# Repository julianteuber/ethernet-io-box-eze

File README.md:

View this project on [CADLAB.io](https://cadlab.io/project/2373). 

# ethernet_io_box_eze

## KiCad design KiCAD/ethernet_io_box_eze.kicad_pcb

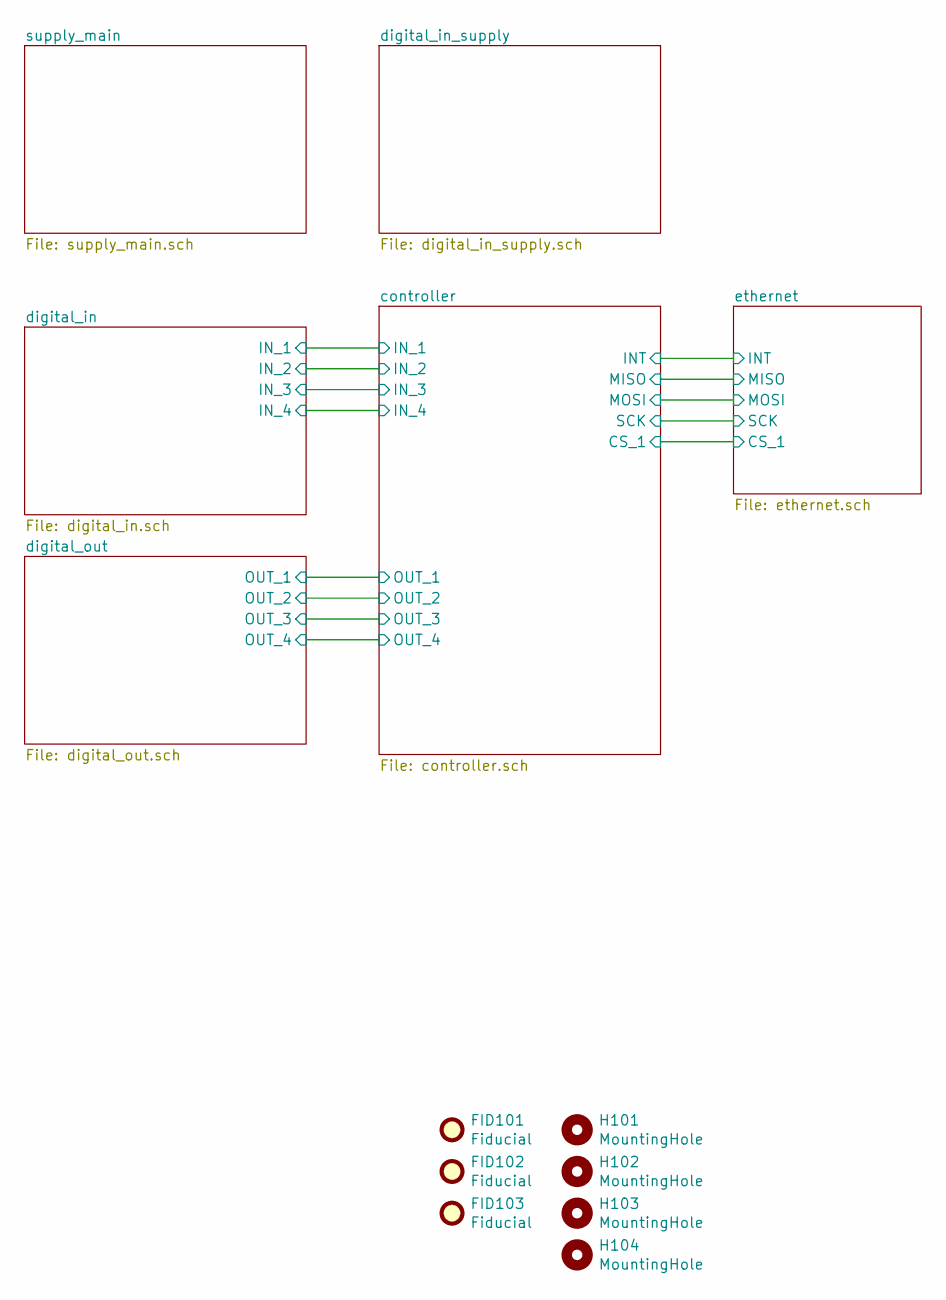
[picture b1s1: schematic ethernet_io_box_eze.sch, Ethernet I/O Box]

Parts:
FID101, FID102, FID103: Fiducial; Fiducial_0.5mm_Mask1mm
H101, H102, H103, H104: MountingHole; MountingHole_3mm

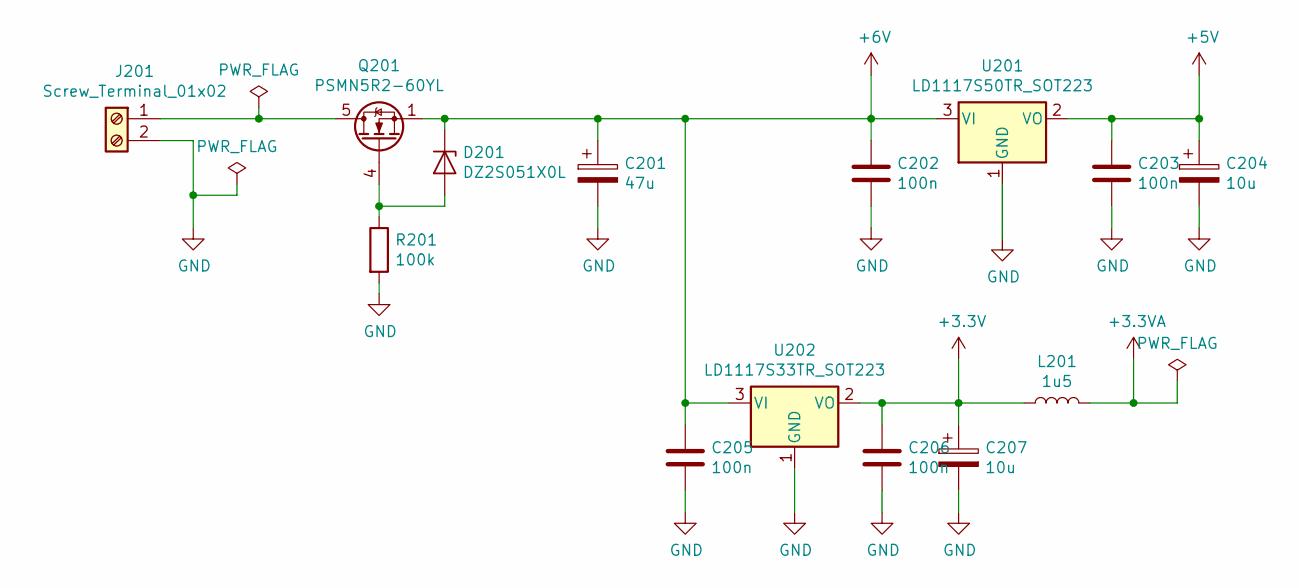
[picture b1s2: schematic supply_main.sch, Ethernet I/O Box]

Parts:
C201: 47u; CP_Elec_6.3x5.9
C202, C203, C205, C206: 100n; C_0805_2012Metric
C204, C207: 10u; CP_Elec_6.3x5.8
D201: DZ2S051X0L; D_SOD-523
J201: Screw_Terminal_01x02; PhoenixContact_GMSTBVA_2,5_2-G-7,62_1x02_P7.62mm_Vertical
L201: 1u5; L_0805_2012Metric
Q201: PSMN5R2-60YL; LFPAK56
R201: 100k; R_0805_2012Metric
U201: LD1117S50TR_SOT223; SOT-223-3_TabPin2
U202: LD1117S33TR_SOT223; SOT-223-3_TabPin2

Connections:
+3.3VA: L201.2; also elsewhere on the board
+3V3: C206.1, C207.1, L201.1, U202.2 (VO); also elsewhere on the board
+5V: C203.1, C204.1, U201.2 (VO); also elsewhere on the board
+6V: C201.1, C202.1, C205.1, D201.1 (K), Q201.1 (S), Q201.2 (S), Q201.3 (S), U201.3 (VI), U202.3 (VI); also elsewhere on the board
GND: C201.2, C202.2, C203.2, C204.2, C205.2, C206.2, C207.2, J201.2, R201.2, U201.1 (GND), U202.1 (GND); also elsewhere on the board
unnamed: D201.2 (A), Q201.4 (G), R201.1
unnamed: J201.1, Q201.5 (D)

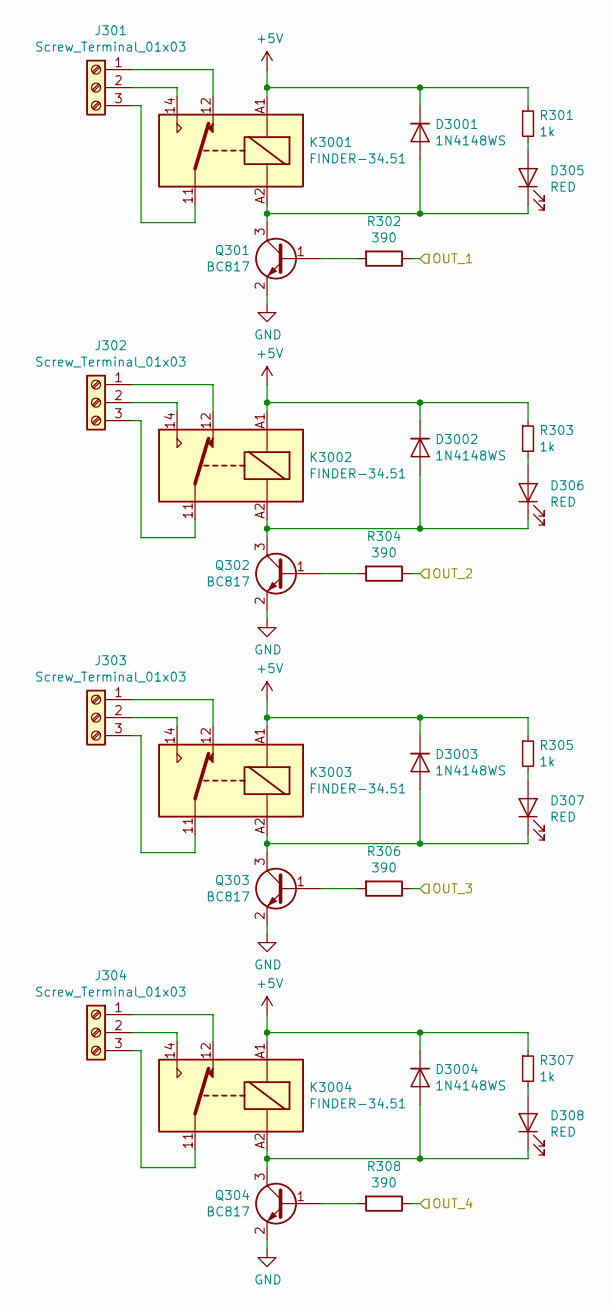
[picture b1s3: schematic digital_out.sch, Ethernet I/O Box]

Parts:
D305, D306, D307, D308: RED; LED_0805_2012Metric
D3001, D3002, D3003, D3004: 1N4148WS; D_SOD-123
J301, J302, J303, J304: Screw_Terminal_01x03; PhoenixContact_GMSTBVA_2,5_3-G-7,62_1x03_P7.62mm_Vertical
K3001, K3002, K3003, K3004: FINDER-34.51; Relay_SPDT_Finder_34.51_Vertical
Q301, Q302, Q303, Q304: BC817; SOT-23
R301, R303, R305, R307: 1k; R_0805_2012Metric
R302, R304, R306, R308: 390; R_0805_2012Metric

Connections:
+5V: D3001.1 (K), D3002.1 (K), D3003.1 (K), D3004.1 (K), K3001.A1, K3002.A1, K3003.A1, K3004.A1, R301.1, R303.1, R305.1, R307.1; also elsewhere on the board
/controller/OUT_1: R302.1; also elsewhere on the board
/controller/OUT_2: R304.1; also elsewhere on the board
/controller/OUT_3: R306.1; also elsewhere on the board
/controller/OUT_4: R308.1; also elsewhere on the board
GND: Q301.2 (E), Q302.2 (E), Q303.2 (E), Q304.2 (E); also elsewhere on the board
unnamed: D305.2 (A), R301.2
unnamed: D306.2 (A), R303.2
unnamed: D307.2 (A), R305.2
unnamed: D308.2 (A), R307.2
unnamed: D305.1 (K), D3001.2 (A), K3001.A2, Q301.3 (C)
unnamed: D306.1 (K), D3002.2 (A), K3002.A2, Q302.3 (C)
unnamed: D307.1 (K), D3003.2 (A), K3003.A2, Q303.3 (C)
unnamed: D308.1 (K), D3004.2 (A), K3004.A2, Q304.3 (C)
unnamed: J301.1, K3001.12
unnamed: J301.2, K3001.14
unnamed: J301.3, K3001.11
unnamed: J302.1, K3002.12
unnamed: J302.2, K3002.14
unnamed: J302.3, K3002.11
unnamed: J303.1, K3003.12
unnamed: J303.2, K3003.14
unnamed: J303.3, K3003.11
unnamed: J304.1, K3004.12
unnamed: J304.2, K3004.14
unnamed: J304.3, K3004.11
unnamed: Q301.1 (B), R302.2
unnamed: Q302.1 (B), R304.2
unnamed: Q303.1 (B), R306.2
unnamed: Q304.1 (B), R308.2

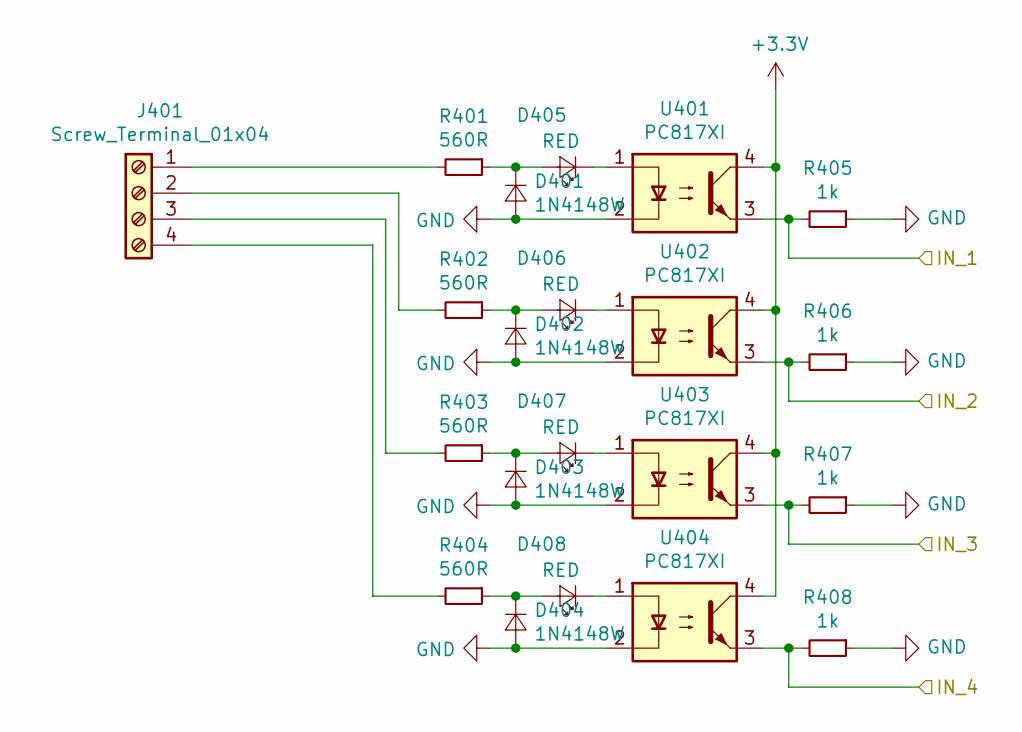
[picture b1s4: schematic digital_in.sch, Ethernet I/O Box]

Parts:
D401, D402, D403, D404: 1N4148W; D_SOD-123
D405, D406, D407, D408: RED; LED_0805_2012Metric
J401: Screw_Terminal_01x04; PhoenixContact_GMSTBVA_2,5_4-G-7,62_1x04_P7.62mm_Vertical
R401, R402, R403, R404: 560R; R_0805_2012Metric
R405, R406, R407, R408: 1k; R_0805_2012Metric
U401, U402, U403, U404: PC817XI; DIP-4_W8.89mm_SMDSocket_LongPads

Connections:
+3V3: U401.4, U402.4, U403.4, U404.4; also elsewhere on the board
/controller/IN_1: R405.2, U401.3; also elsewhere on the board
/controller/IN_2: R406.2, U402.3; also elsewhere on the board
/controller/IN_3: R407.2, U403.3; also elsewhere on the board
/controller/IN_4: R408.2, U404.3; also elsewhere on the board
GND: D401.2 (A), D402.2 (A), D403.2 (A), D404.2 (A), R405.1, R406.1, R407.1, R408.1, U401.2, U402.2, U403.2, U404.2; also elsewhere on the board
unnamed: D401.1 (K), D405.2 (A), R401.1
unnamed: D402.1 (K), D406.2 (A), R402.1
unnamed: D403.1 (K), D407.2 (A), R403.1
unnamed: D404.1 (K), D408.2 (A), R404.1
unnamed: D405.1 (K), U401.1
unnamed: D406.1 (K), U402.1
unnamed: D407.1 (K), U403.1
unnamed: D408.1 (K), U404.1
unnamed: J401.1, R401.2
unnamed: J401.2, R402.2
unnamed: J401.3, R403.2
unnamed: J401.4, R404.2

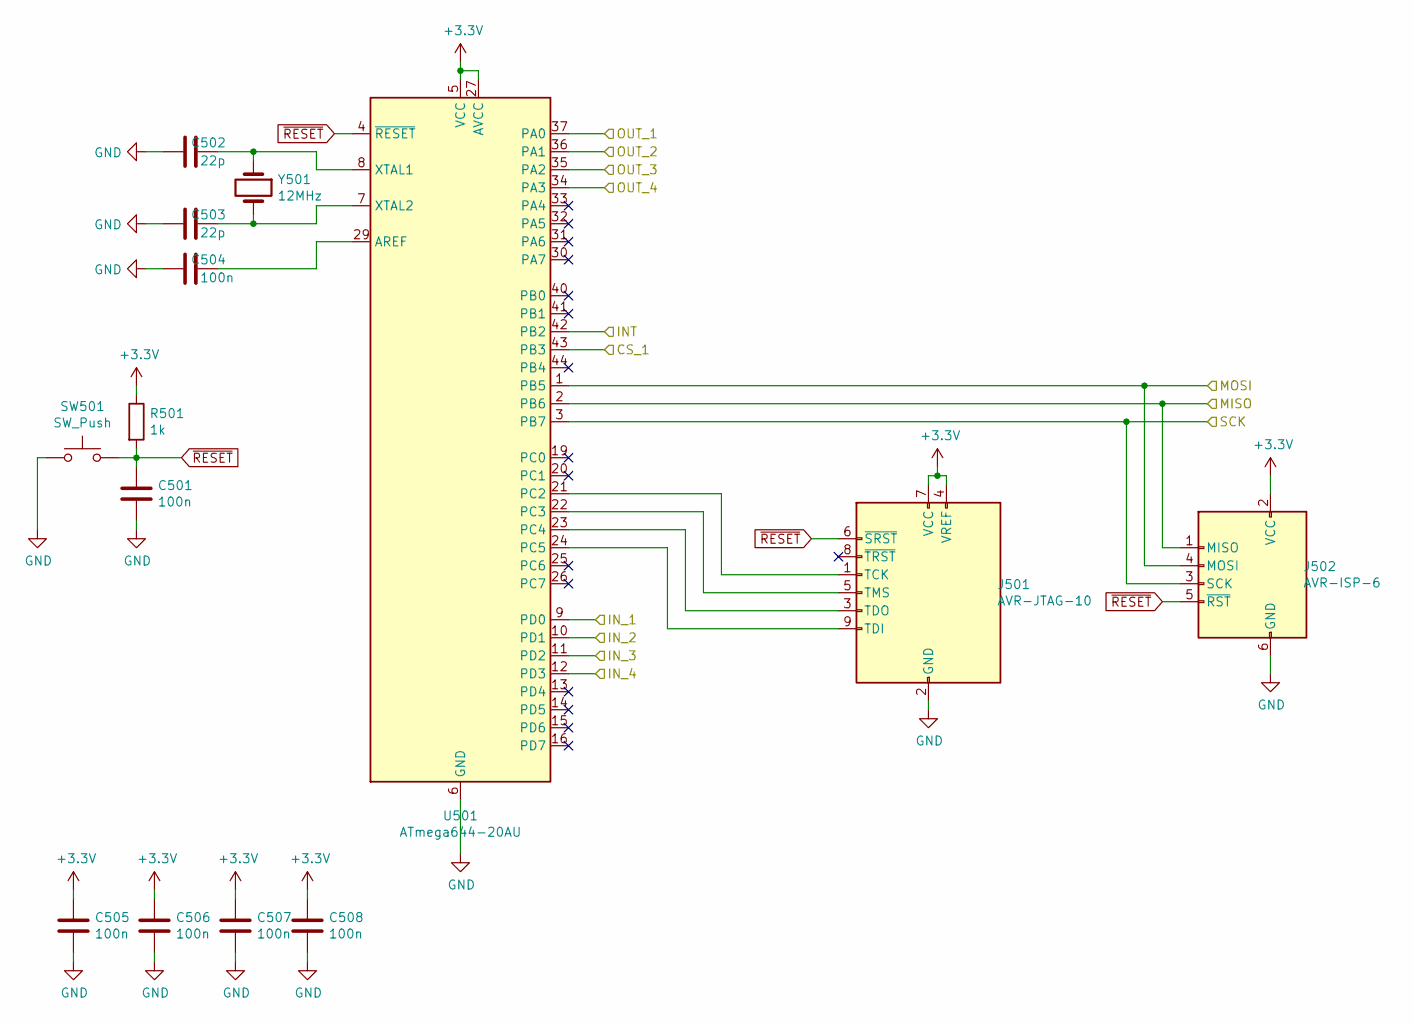
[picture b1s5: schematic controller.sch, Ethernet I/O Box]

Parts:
C501, C504, C505, C506, C507, C508: 100n; C_0805_2012Metric
C502, C503: 22p; C_0805_2012Metric
J501: AVR-JTAG-10; IDC-Header_2x05_P2.54mm_Vertical
J502: AVR-ISP-6; IDC-Header_2x03_P2.54mm_Vertical
R501: 1k; R_0805_2012Metric
SW501: SW_Push; SW_SPST_B3U-1000P
U501: ATmega644-20AU; TQFP-44_10x10mm_P0.8mm
Y501: 12MHz; Crystal_SMD_MicroCrystal_CC7V-T1A-2Pin_3.2x1.5mm

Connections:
+3V3: C505.1, C506.1, C507.1, C508.1, J501.4 (VREF), J501.7 (VCC), J502.2 (VCC), R501.1, U501.5 (VCC), U501.17 (VCC), U501.27 (AVCC), U501.38 (VCC); also elsewhere on the board
/controller/CS_1: U501.43 (PB3); also elsewhere on the board
/controller/INT: U501.42 (PB2); also elsewhere on the board
/controller/IN_1: U501.9 (PD0); also elsewhere on the board
/controller/IN_2: U501.10 (PD1); also elsewhere on the board
/controller/IN_3: U501.11 (PD2); also elsewhere on the board
/controller/IN_4: U501.12 (PD3); also elsewhere on the board
/controller/MISO: J502.1 (MISO), U501.2 (PB6); also elsewhere on the board
/controller/MOSI: J502.4 (MOSI), U501.1 (PB5); also elsewhere on the board
/controller/OUT_1: U501.37 (PA0); also elsewhere on the board
/controller/OUT_2: U501.36 (PA1); also elsewhere on the board
/controller/OUT_3: U501.35 (PA2); also elsewhere on the board
/controller/OUT_4: U501.34 (PA3); also elsewhere on the board
/controller/SCK: J502.3 (SCK), U501.3 (PB7); also elsewhere on the board
GND: C501.2, C502.2, C503.2, C504.2, C505.2, C506.2, C507.2, C508.2, J501.2 (GND), J501.10 (GND), J502.6 (GND), SW501.1, U501.6 (GND), U501.18 (GND), U501.28 (GND), U501.39 (GND); also elsewhere on the board
unnamed: C502.1, U501.8 (XTAL1), Y501.1
unnamed: C503.1, U501.7 (XTAL2), Y501.2
unnamed: C504.1, U501.29 (AREF)
unnamed: J501.1 (TCK), U501.21 (PC2)
unnamed: J501.3 (TDO), U501.23 (PC4)
unnamed: J501.5 (TMS), U501.22 (PC3)
unnamed: J501.9 (TDI), U501.24 (PC5)
~RESET: C501.1, J501.6 (~SRST), J502.5 (~RST), R501.2, SW501.2, U501.4 (~RESET)

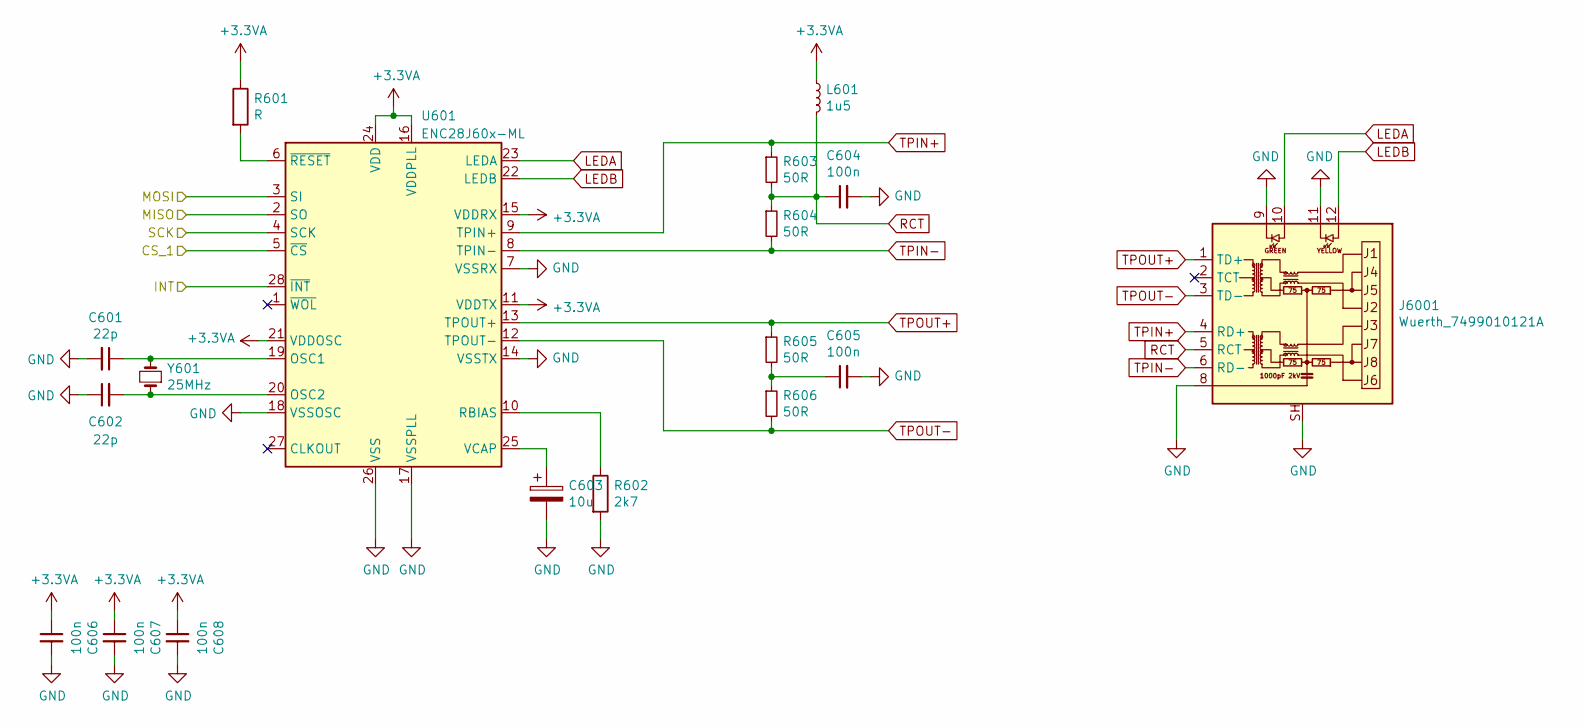
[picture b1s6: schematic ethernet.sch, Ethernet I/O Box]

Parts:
C601, C602: 22p; C_0805_2012Metric
C603: 10u; CP_Elec_6.3x5.8
C604, C605, C606, C607, C608: 100n; C_0805_2012Metric
J6001: Wuerth_7499010121A; RJ45_Wuerth_7499010121A_Horizontal
L601: 1u5; L_0805_2012Metric
R601: R; R_0805_2012Metric
R602: 2k7; R_0805_2012Metric
R603, R604, R605, R606: 50R; R_0805_2012Metric
U601: ENC28J60x-ML; QFN-28-1EP_6x6mm_P0.65mm_EP4.25x4.25mm
Y601: 25MHz; Crystal_SMD_MicroCrystal_CC7V-T1A-2Pin_3.2x1.5mm

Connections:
+3.3VA: C606.1, C607.1, C608.1, L601.1, R601.1, U601.11 (VDDTX), U601.15 (VDDRX), U601.16 (VDDPLL), U601.21 (VDDOSC), U601.24 (VDD); also elsewhere on the board
/controller/CS_1: U601.5 (~CS); also elsewhere on the board
/controller/INT: U601.28 (~INT); also elsewhere on the board
/controller/MISO: U601.2 (SO); also elsewhere on the board
/controller/MOSI: U601.3 (SI); also elsewhere on the board
/controller/SCK: U601.4 (SCK); also elsewhere on the board
GND: C601.2, C602.1, C603.2, C604.2, C605.2, C606.2, C607.2, C608.2, J6001.8, J6001.9, J6001.11, J6001.SH, R602.2, U601.7 (VSSRX), U601.14 (VSSTX), U601.17 (VSSPLL), U601.18 (VSSOSC), U601.26 (VSS); also elsewhere on the board
LEDA: J6001.10, U601.23 (LEDA)
LEDB: J6001.12, U601.22 (LEDB)
unnamed: C601.1, U601.19 (OSC1), Y601.2
unnamed: C602.2, U601.20 (OSC2), Y601.1
unnamed: C603.1, U601.25 (VCAP)
unnamed: C605.1, R605.2, R606.1
unnamed: R601.2, U601.6 (~RESET)
unnamed: R602.1, U601.10 (RBIAS)
RCT: C604.1, J6001.5 (RCT), L601.2, R603.2, R604.1
TPIN+: J6001.4 (RD+), R603.1, U601.9 (TPIN+)
TPIN-: J6001.6 (RD-), R604.2, U601.8 (TPIN-)
TPOUT+: J6001.1 (TD+), R605.1, U601.13 (TPOUT+)
TPOUT-: J6001.3 (TD-), R606.2, U601.12 (TPOUT-)

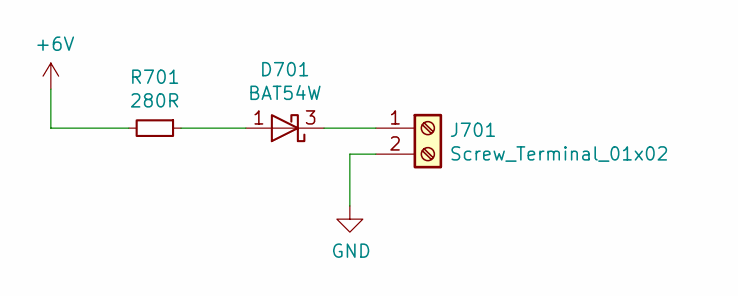
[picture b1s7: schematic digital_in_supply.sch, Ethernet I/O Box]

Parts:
D701: BAT54W; SOT-323_SC-70
J701: Screw_Terminal_01x02; PhoenixContact_GMSTBVA_2,5_2-G-7,62_1x02_P7.62mm_Vertical
R701: 280R; R_0805_2012Metric

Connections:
+6V: R701.2; also elsewhere on the board
GND: J701.2; also elsewhere on the board
unnamed: D701.1 (A), R701.1
unnamed: D701.3 (K), J701.1

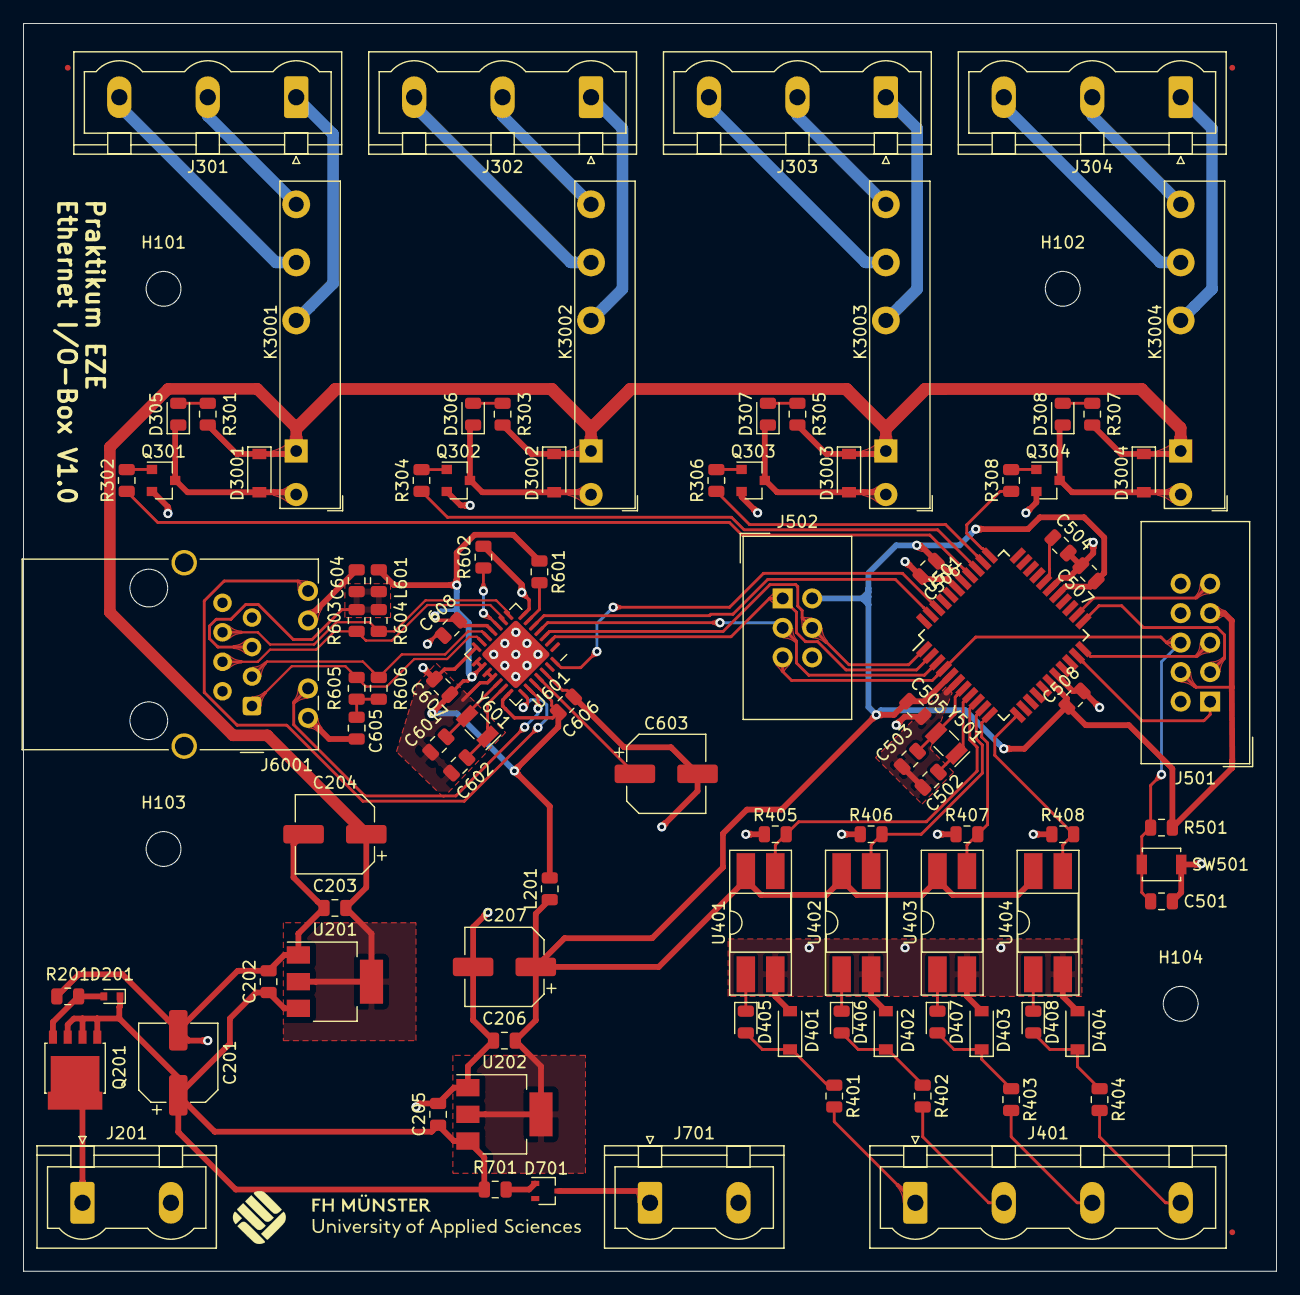
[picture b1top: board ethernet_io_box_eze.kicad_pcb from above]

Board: 2 copper layers, 108.0 x 107.5 mm, 105 parts (0 on the bottom side), 79 nets.

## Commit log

2019-12-21 Added folders KiCAD and mechanics
2019-12-23 Added .gitignore file.
2019-12-23 Removed files from repository previously commited and now covered by .gitignore
2019-12-23 Backlink to CADLAB.io has been added.
2019-12-30 Added fiducials, ignoring netlist
2020-01-06 Moved reset button. Added the FH-Muenster logo on silk-screen.
2020-01-07 Added teardrops. Changes clearance setting in board setup from 1 mm to 5 5mm for 230 net.
